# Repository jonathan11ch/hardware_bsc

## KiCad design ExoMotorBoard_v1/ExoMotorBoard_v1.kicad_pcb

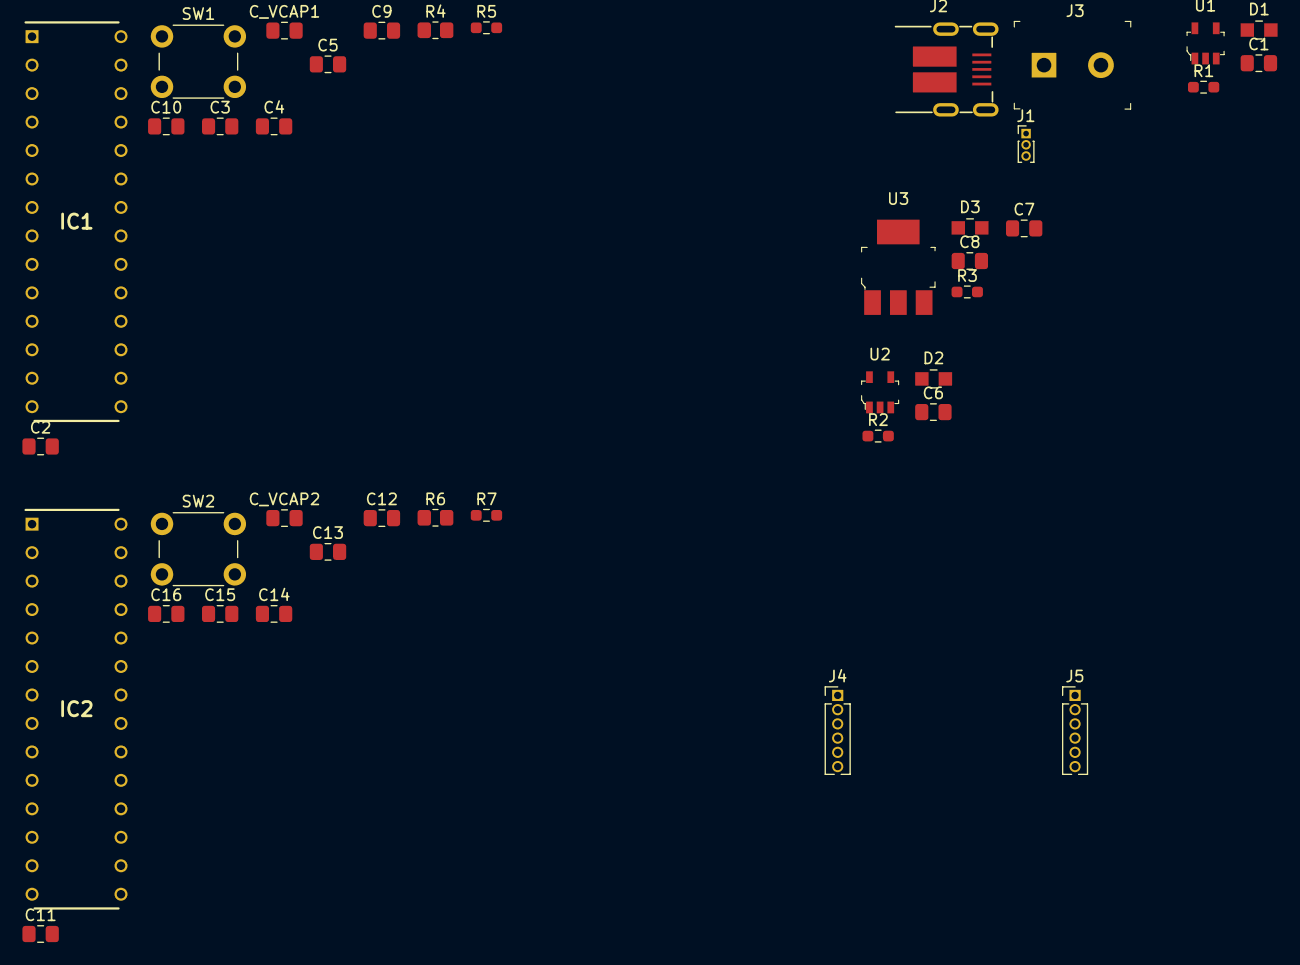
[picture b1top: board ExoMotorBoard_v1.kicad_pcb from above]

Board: 2 copper layers, 40 parts (0 on the bottom side), 22 nets, no tracks yet.

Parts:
C1, C6: 1uF; C_0805_2012Metric_Pad1.18x1.45mm_HandSolder
C2, C3, C4, C5, C9, C10, C11, C12, C13, C14, C15, C16: 0.1uF; C_0805_2012Metric_Pad1.18x1.45mm_HandSolder
C7, C8: 10uF; C_0805_2012Metric_Pad1.18x1.45mm_HandSolder
C_VCAP1, C_VCAP2: 10uF; C_0805_2012Metric_Pad1.18x1.45mm_HandSolder
D1, D2, D3: LG_R971-KN-1; 0805
IC1, IC2: DSPIC33FJ128MC802-I_SP; DIP794W56P254L3486H508Q28N
J1: Conn_01x03_Male; PinHeader_1x03_P1.00mm_Vertical
J2: UJ2-MIBH-4-SMT-TR; USB_Micro_B_Male_UJ2-MIBH-4-SMT-TR
J3: OSTTC022162; Term_Block_1x2_P5.08MM
J4, J5: Conn_01x06_Male; PinHeader_1x06_P1.27mm_Vertical
R1, R2, R3: 3.3k; R_0603_1608Metric_Pad0.98x0.95mm_HandSolder
R4, R6: 10k; R_0805_2012Metric_Pad1.20x1.40mm_HandSolder
R5, R7: 400; R_0603_1608Metric_Pad0.98x0.95mm_HandSolder
SW1, SW2: SW_Push_Dual; SW_PUSH_6mm_H5mm
U1, U2: MIC5219-3_3YM5-TR; SOT-753
U3: NCP1117ST50T3G; SOT-223

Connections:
+5V: C8.1, R3.1, U3.2
/MCU_Circuit1/AN2_INPUT: IC1.4, J4.4
/MCU_Circuit1/AN3_INPUT: IC1.5, J4.5
/MCU_Circuit1/AVSS: C10.2, IC1.27
/MCU_Circuit1/MSCLR: IC1.1, J4.1, R5.1
/MCU_Circuit1/VCAP: C_VCAP1.2, IC1.20
/MCU_Circuit2/AN2_INPUT: IC2.4, J5.4
/MCU_Circuit2/AN3_INPUT: IC2.5, J5.5
/MCU_Circuit2/AVSS: C16.2, IC2.27
/MCU_Circuit2/MSCLR: IC2.1, J5.1, R7.1
/MCU_Circuit2/VCAP: C_VCAP2.2, IC2.20
/PowerCircuit/V_USB: J1.1, J2.1
/PowerCircuit/V_ext: J1.3, J3.1
/PowerCircuit/Vin: C7.1, J1.2, U1.1, U1.3, U2.1, U2.3, U3.3
/VDD_1: C1.1, C2.1, C3.1, C4.1, C5.1, C9.1, C10.1, IC1.13, IC1.28, J4.2, R1.1, R4.1, U1.5
/VDD_2: C6.1, C11.1, C12.1, C13.1, C14.1, C15.1, C16.1, IC2.13, IC2.28, J5.2, R2.1, R6.1, U2.5
GND: C1.2, C2.2, C3.2, C4.2, C5.2, C6.2, C7.2, C8.2, C9.2, C11.2, C12.2, C13.2, C14.2, C15.2, C_VCAP1.1, C_VCAP2.1, D1.2, D2.2, D3.2, IC1.8, IC1.19, IC2.8, IC2.19, J2.5, J2.SH, J3.2, J4.3, J5.3, SW1.2, SW2.2, U1.2, U2.2, U3.1
unnamed: D1.1, R1.2
unnamed: D2.1, R2.2
unnamed: D3.1, R3.2
unnamed: R4.2, R5.2, SW1.1
unnamed: R6.2, R7.2, SW2.1

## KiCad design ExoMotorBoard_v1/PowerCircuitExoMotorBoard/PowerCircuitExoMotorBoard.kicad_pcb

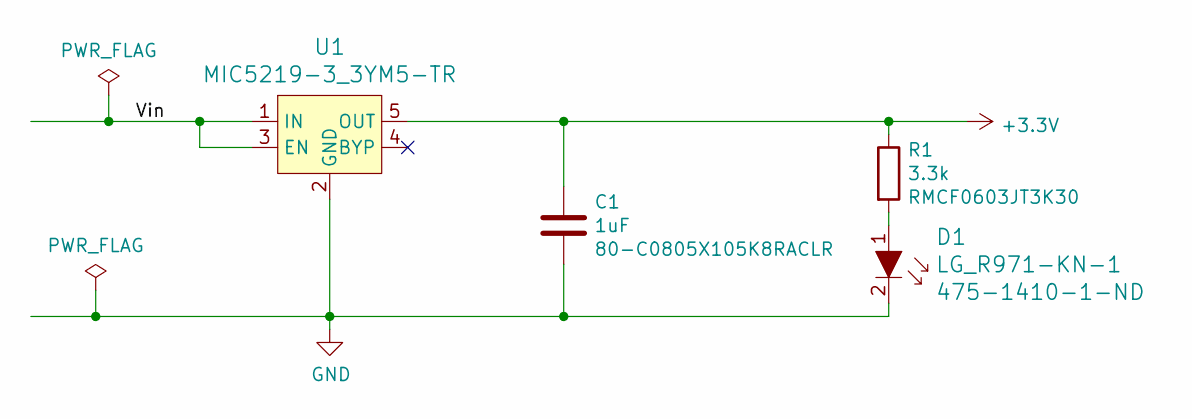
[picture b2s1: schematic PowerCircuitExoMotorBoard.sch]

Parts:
C1: 1uF; C_0805_2012Metric_Pad1.18x1.45mm_HandSolder; Mouser 80-C0805X105K8RACLR
D1: LG_R971-KN-1; 0805; MPN LG R971-KN-1; Digi-Key_PN 475-1410-1-ND
R1: 3.3k; R_0603_1608Metric_Pad0.98x0.95mm_HandSolder; Digi-Key_PN RMCF0603JT3K30
U1: MIC5219-3_3YM5-TR; SOT-753; MPN MIC5219-3.3YM5-TR; Digi-Key_PN 576-1281-1-ND

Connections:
+3V3: C1.1, R1.1, U1.5 (OUT)
/Vin: U1.1 (IN), U1.3 (EN)
GND: C1.2, D1.2, U1.2 (GND)
unnamed: D1.1, R1.2

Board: 2 copper layers, 4 parts (0 on the bottom side), 4 nets, no tracks yet.

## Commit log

2021-08-02 Kicad project setup
2021-08-02 added kicad library for DSPIC33fj128mc802
2021-08-03 Updated micro library files
2021-08-05 3.3v regulator circuit updated
2021-08-06 Kicad project organized by modular sheets
2021-08-11 MCU schematic connections updated
2021-08-16 MCU connection updated
2021-08-16 Encoder connectors added in the schematic
2021-08-17 UART1 Connections added in MCU
2021-09-28 updated pins in the MCU circuit
